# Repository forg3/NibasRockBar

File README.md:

# NibasRockBar — Pulseira Inteligente de Identificação e Localização

Sistema de pulseira eletrônica (NFC + BLE) para identificação de clientes e localização
indoor no salão, integrado ao sistema de caixa **Deli**. Atendimento continua 100% humano —
garçom tira o pedido, equipe serve bebidas e a cozinha prepara os pratos. A pulseira só
identifica o cliente e ajuda a equipe a localizá-lo mais rápido.

## Fluxo do produto

1. **Check-in** — cliente recebe uma pulseira livre; o sistema abre a comanda no Deli.
2. **Pedido** — garçom lê a pulseira (NFC) e lança o pedido na comanda certa, em qualquer mesa.
3. **Localização** — o app do garçom mostra a área do salão onde cada comanda está (BLE).
4. **Conferência e saída** — caixa fecha a comanda no Deli, cliente paga, pulseira libera
   sozinha para o próximo cliente.

## Estrutura do repositório

| Caminho | Conteúdo |
|---|---|
| `PROPOSTA_SMART_BADGE_PUB_v3.md` | Especificação do produto (hardware, fluxo, fabricação) |
| `proposta_proprietario.html` | Proposta visual para apresentar ao proprietário do pub |
| `modelo_3d_prototipo.html` | Modelo 3D interativo do protótipo (pulseira + disco) |
| `ORCAMENTO_PROTOTIPAGEM.md` | Orçamento detalhado para 5 unidades protótipo |
| `BOM_custos_prototipos.csv` | BOM com custo por unidade (lote de teste) |
| `BOM_smartbadge_v2.csv` | BOM recomendada (módulo BLE certificado) |
| `BOM_discreta_corrigida_nRF52810_QFN32.csv` | BOM alternativa (SoC discreto), pinagem verificada no datasheet Nordic |
| `netlist_conexoes.md` | Tabela de conexões pino a pino, pronta para KiCad |
| `RELATORIO_REVISAO_TECNICA.md` | Revisão técnica completa (matemática de bateria, RF, RSSI, NFC) |
| `firmware/main.c` | Firmware da pulseira (nRF5 SDK) — beacon BLE + leitura de bateria |
| `firmware/nrf/` | Projeto de compilação nRF5 SDK 17.1.0 (pca10040e/s112, nRF52810 + SoftDevice S112 7.2.0) — compila com `make -C firmware/nrf/armgcc` (requer `arm-none-eabi-gcc`) |
| `gateway_esp32/gateway_esp32.ino` | Firmware do gateway de teto (scan BLE + filtro EWMA + MQTT) — compila no Arduino IDE com esquema de partição Huge APP |
| `backend/app.py` | Servidor local (FastAPI) — localização por RSSI + inventário de pulseiras |
| `backend/deli_adapter.py` | Integração real com a API pública do Deli (plataforma Fudo) |
| `integracao_deli/README.md` | Como habilitar e usar a API do Deli |
| `hardware/kicad/docs/decisao_forma_fisica.md` | Decisão da variante A: troca do módulo E73 pelo Fanstel BM832A |
| `hardware/kicad/docs/layout_status.md` | Estado atual dos layouts das placas |
| `hardware/kicad/docs/procedimento_vna.md` | Procedimento de tuning da antena/RF com VNA |
| `hardware/kicad/docs/cotacao_fabricacao.md` | Cotação de fabricação (com GATE — nada submetido ainda) |
| `hardware/kicad/*/exports/fab/` | Pacote de fabricação gerado (Gerbers, furação, BOM, posição) |
| `docs/security-audit/relatorio-auditoria-seguranca.pdf` | Relatório da auditoria de segurança |

## Arquitetura (visão geral)

```
Pulseira (NFC + BLE) ──► Gateway ESP32 (scan BLE) ──► MQTT ──► Backend local (FastAPI)
                                                                      │
                                                                      ├─► Localização por mesa/zona
                                                                      └─► Deli API (abre/monitora comanda)

Garçom (app/tablet) ──► lê NFC da pulseira ──► lança pedido direto no Deli
```

- **Identificação (NFC)**: tag passiva na pulseira, lida pelo garçom para abrir/lançar pedidos.
- **Localização (BLE)**: pulseira transmite beacon; gateways de teto (ESP32) captam RSSI e
  publicam via MQTT; o backend decide a zona mais próxima (vizinho mais próximo com histerese).
- **Caixa/pagamento**: sempre no Deli — este projeto não duplica cardápio, pagamento nem fiscal.

## Como rodar o backend localmente

```bash
cd backend
pip install -r requirements.txt
export DELI_API_KEY="..."
export DELI_API_SECRET="..."
export NIBAS_API_KEY="..."  # exigida em toda chamada via header X-API-Key
uvicorn app:app --host 0.0.0.0 --port 8000
```

Requer um broker MQTT local (ex: Mosquitto) publicando em `pub/telemetria/#`.

## Hardware

- Disco Ø32 mm, cápsula IP67, pulseira esportiva de silicone.
- Identificação: NXP NTAG213 (inlay pronto, 25 mm).
- Localização (variante A): módulo **Fanstel BM832A** (SoC Nordic nRF52810) — substitui o
  Ebyte E73, decisão documentada em `hardware/kicad/docs/decisao_forma_fisica.md`.
- Bateria: CR2032 com suporte **Keystone 1060** (SMD — o 1059 é THM e não serve),
  ~1,5–2 anos de autonomia estimada.
- Fabricação recomendada: PCBWay ou JLCPCB, regime turnkey.

Detalhes completos, matemática de engenharia e decisões de projeto: ver
`RELATORIO_REVISAO_TECNICA.md` e `PROPOSTA_SMART_BADGE_PUB_v3.md`.
Estado dos layouts: `hardware/kicad/docs/layout_status.md`.
Tuning da antena/RF: `hardware/kicad/docs/procedimento_vna.md`.

## Fabricação

- Pacote de fabricação gerado em `hardware/kicad/*/exports/fab/` (Gerbers, furação, BOM, posição).
- Cotação e checklist de submissão em `hardware/kicad/docs/cotacao_fabricacao.md` —
  **GATE: nada submetido a fabricante ainda.**

## Segurança

- O backend exige autenticação em toda chamada via header `X-API-Key` (chave em `NIBAS_API_KEY`).
- Relatório da auditoria de segurança em `docs/security-audit/relatorio-auditoria-seguranca.pdf`.

## Status

Fase de especificação e protótipo — orçamento para lote de 5 unidades de teste em
`ORCAMENTO_PROTOTIPAGEM.md`. Integração com o Deli implementada e documentada, pendente de
credenciais reais (`DELI_API_KEY`/`DELI_API_SECRET`) para teste de ponta a ponta.

## Pendências

- ANATEL: item aberto (não bloqueia bancada; confirmar antes de operar com público).
  Homologação vale só para os radiadores intencionais (BM832A e ESP32, 2,4 GHz) — PCB,
  bateria, NFC passiva, ferrite e cápsula não certificam; se os módulos já forem
  homologados, o produto usa processo simplificado com os laudos do módulo (confirmar com OCD).
- BOM raiz: corrigir Keystone 1059 → 1060.
- Alimentação do BM832A: indutores do DC/DC integrados ao módulo (fonte: página oficial
  Fanstel) — fecha o item aberto #2.

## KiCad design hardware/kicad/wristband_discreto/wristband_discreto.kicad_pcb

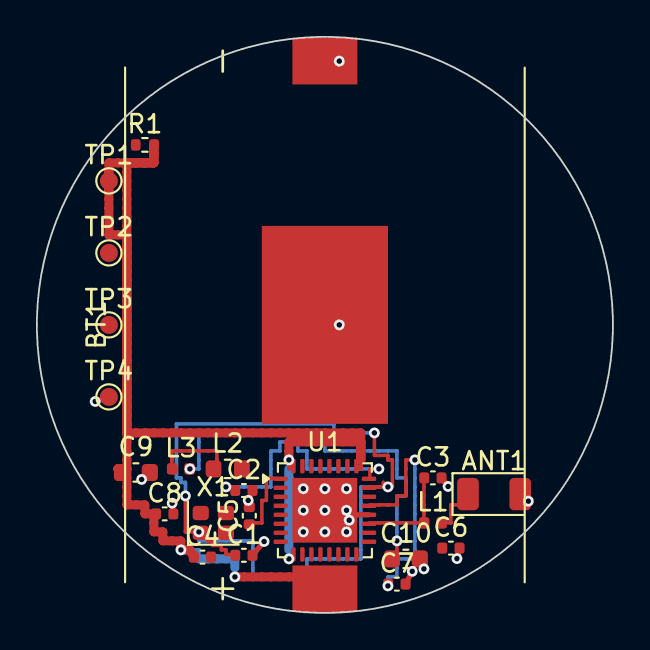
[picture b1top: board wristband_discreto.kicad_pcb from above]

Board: 2 copper layers, 32.0 x 32.0 mm, 23 parts (1 on the bottom side), 15 nets.

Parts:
ANT1: Johanson_2450AT18x100
BT1: Keystone_1060; Keystone_1060_CR2032_SMT
C1, C2, C3, C4, C5, C6, C7, C8: C_0402_1005Metric
C9, C10: C_0603_1608Metric
L1, L3: L_0402_1005Metric
L2: L_0603_1608Metric
R1: R_0402_1005Metric
SHLD1: Ferrite_Shield_22mm; SHLD1_Ferrite_Shield_22mm
TP1, TP2, TP3, TP4: TestPoint_Pad_D1.0mm
U1: QFN-32-1EP_5x5mm_P0.5mm_EP3.6x3.6mm
X1: Crystal_SMD_2016-4Pin_2.0x1.6mm

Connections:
GND: ANT1.2, BT1.2, BT1.3, C1.2, C2.2, C3.2, C4.2, C5.2, C6.2, C7.2, C8.2, C9.2, C10.2, SHLD1.1, TP4.1, U1.20, U1.29, U1.33
NET_ANT: C3.1, L1.1, U1.19
NET_DCC: L2.2, U1.31
NET_DEC1: C5.1, U1.1
NET_DEC2: C7.1, U1.21
NET_DEC3: C6.1, U1.22
NET_DEC4: C10.1, L3.2, U1.30
NET_L2_L3: L2.1, L3.1
NET_RESET: R1.1, U1.16
NET_RF: ANT1.1, L1.2
NET_SWDCLK: TP3.1, U1.17
NET_SWDIO: TP2.1, U1.18
NET_XC1: C1.1, U1.23, X1.1
NET_XC2: C2.1, U1.24, X1.2
VDD_BAT: BT1.1, C4.1, C8.1, C9.1, R1.2, TP1.1, U1.9, U1.25, U1.32

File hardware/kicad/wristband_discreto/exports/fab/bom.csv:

"Refs","Value","Footprint","Qty","DNP"
"ANT1","2450AT18A100E","RF_Antenna:Johanson_2450AT18x100","1",""
"BT1","Keystone_1060","nibas_wristband:Keystone_1060_CR2032_SMT","1",""
"C1","12pF","Capacitor_SMD:C_0402_1005Metric","1",""
"C2","12pF","Capacitor_SMD:C_0402_1005Metric","1",""
"C3","0.8pF","Capacitor_SMD:C_0402_1005Metric","1",""
"C4","100nF","Capacitor_SMD:C_0402_1005Metric","1",""
"C5","100nF","Capacitor_SMD:C_0402_1005Metric","1",""
"C6","100pF","Capacitor_SMD:C_0402_1005Metric","1",""
"C7","100nF","Capacitor_SMD:C_0402_1005Metric","1","DNP"
"C8","100nF","Capacitor_SMD:C_0402_1005Metric","1",""
"C9","4.7uF","Capacitor_SMD:C_0603_1608Metric","1",""
"C10","1.0uF","Capacitor_SMD:C_0603_1608Metric","1",""
"L1","3.9nH","Inductor_SMD:L_0402_1005Metric","1",""
"L2","10uH","Inductor_SMD:L_0603_1608Metric","1",""
"L3","15nH","Inductor_SMD:L_0402_1005Metric","1",""
"R1","10k","Resistor_SMD:R_0402_1005Metric","1","DNP"
"SHLD1","Ferrite_Shield","nibas_wristband:SHLD1_Ferrite_Shield_22mm","1",""
"TAG1","NTAG213_Inlay","nibas_wristband:NTAG213_Inlay_25mm","1",""
"TP1","TestPoint","TestPoint:TestPoint_Pad_D1.0mm","1",""
"TP2","TestPoint","TestPoint:TestPoint_Pad_D1.0mm","1",""
"TP3","TestPoint","TestPoint:TestPoint_Pad_D1.0mm","1",""
"TP4","TestPoint","TestPoint:TestPoint_Pad_D1.0mm","1",""
"U1","nRF52810-QCAA","Package_DFN_QFN:QFN-32-1EP_5x5mm_P0.5mm_EP3.6x3.6mm","1",""
"X1","32MHz CL=8pF","Crystal:Crystal_SMD_2016-4Pin_2.0x1.6mm","1",""

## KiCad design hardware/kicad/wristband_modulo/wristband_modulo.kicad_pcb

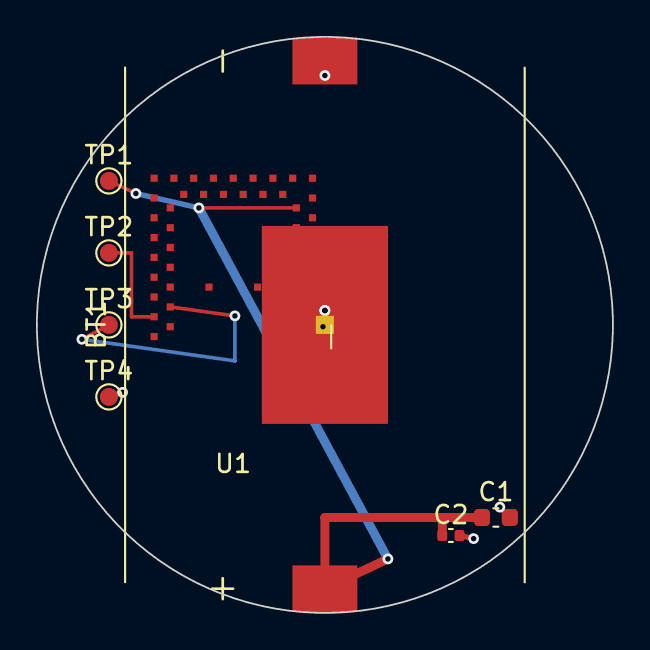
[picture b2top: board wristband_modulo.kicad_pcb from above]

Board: 2 copper layers, 32.0 x 32.0 mm, 9 parts (1 on the bottom side), 4 nets.

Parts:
BT1: Keystone_1060; Keystone_1060_CR2032_SMT
C1: C_0603_1608Metric
C2: C_0402_1005Metric
SHLD1: Ferrite_Shield_22mm; SHLD1_Ferrite_Shield_22mm
TP1, TP2, TP3, TP4: TestPoint_Pad_D1.0mm
U1: BM832A

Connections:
GND: BT1.2, BT1.3, C1.2, C2.2, SHLD1.1, TP4.1, U1.1
NET_SWDCLK: TP3.1, U1.42
NET_SWDIO: TP2.1, U1.43
VDD_BAT: BT1.1, C1.1, C2.1, TP1.1, U1.14

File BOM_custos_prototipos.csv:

Designator,Componente,Fonte de preco,Preco unitario USD (qtd. protótipo),Qtd por unidade,Custo por unidade USD
U1,Modulo BLE certificado (ex: Raytac MDBT42Q-512KV2),LCSC/DigiKey - preco unitario verificado,6.50,1,6.50
TAG1,NTAG213 inlay adesivo 25mm,Varejo BR (pacotes pequenos) - preco unitario verificado,1.00,1,1.00
SHLD1,Folha de ferrite blindagem ~20mm,Estimativa (folha cortada sob medida),0.80,1,0.80
BT1,Suporte CR2032 Keystone 1060 (SMT; 1059 é THM),Estimativa distribuidor,0.40,1,0.40
BAT1,Bateria CR2032,Estimativa distribuidor,0.30,1,0.30
C1,Capacitor 10uF 0603,Estimativa distribuidor,0.10,1,0.10
C2,Capacitor 100nF 0402,Estimativa distribuidor,0.05,1,0.05
--,Capsula SLA (2 partes) + O-ring,Estimativa servico PCBWay/Seeed SLA,10.50,1,10.50
--,Berco de pulseira esportiva (comprado pronto),Estimativa varejo,3.00,1,3.00
--,Mao de obra de montagem (por unidade - alem do NRE),Estimativa PCBA baixo volume,12.00,1,12.00
,,,,TOTAL POR UNIDADE (sem NRE),34.65

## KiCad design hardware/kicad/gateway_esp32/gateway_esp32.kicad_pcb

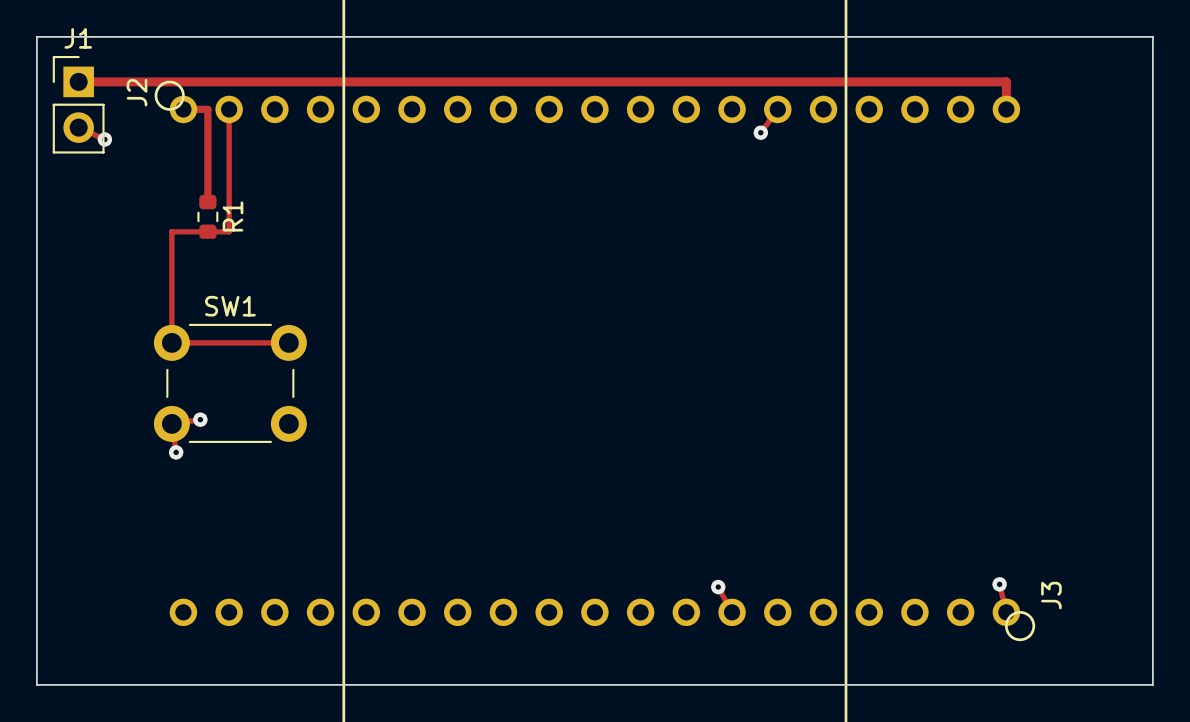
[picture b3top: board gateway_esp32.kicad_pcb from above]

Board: 2 copper layers, 62.0 x 36.0 mm, 4 parts (0 on the bottom side), 4 nets.

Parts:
J1: PinHeader_1x02_P2.54mm_Vertical
R1: R_0603_1608Metric
SW1: SW_PUSH_6mm
U1: ESP32-DevKitC-32E; ESP32-DevKitC-32E_Carrier

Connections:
+3V3: R1.1, U1.1
+5V: J1.1, U1.19
EN: R1.2, SW1.1, U1.2
GND: J1.2, SW1.2, U1.14, U1.20, U1.26

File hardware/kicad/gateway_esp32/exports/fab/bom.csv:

"Refs","Value","Footprint","Qty","DNP"
"J1","USB-C 5V power-only ou terminal 2p","Connector_PinHeader_2.54mm:PinHeader_1x02_P2.54mm_Vertical","1",""
"R1","10k","Resistor_SMD:R_0603_1608Metric","1",""
"SW1","Botao reset EN (NA)","Button_Switch_THT:SW_PUSH_6mm","1",""
"U1","ESP32-DevKitC-32E","nibas_gateway:ESP32-DevKitC-32E_Carrier","1",""
